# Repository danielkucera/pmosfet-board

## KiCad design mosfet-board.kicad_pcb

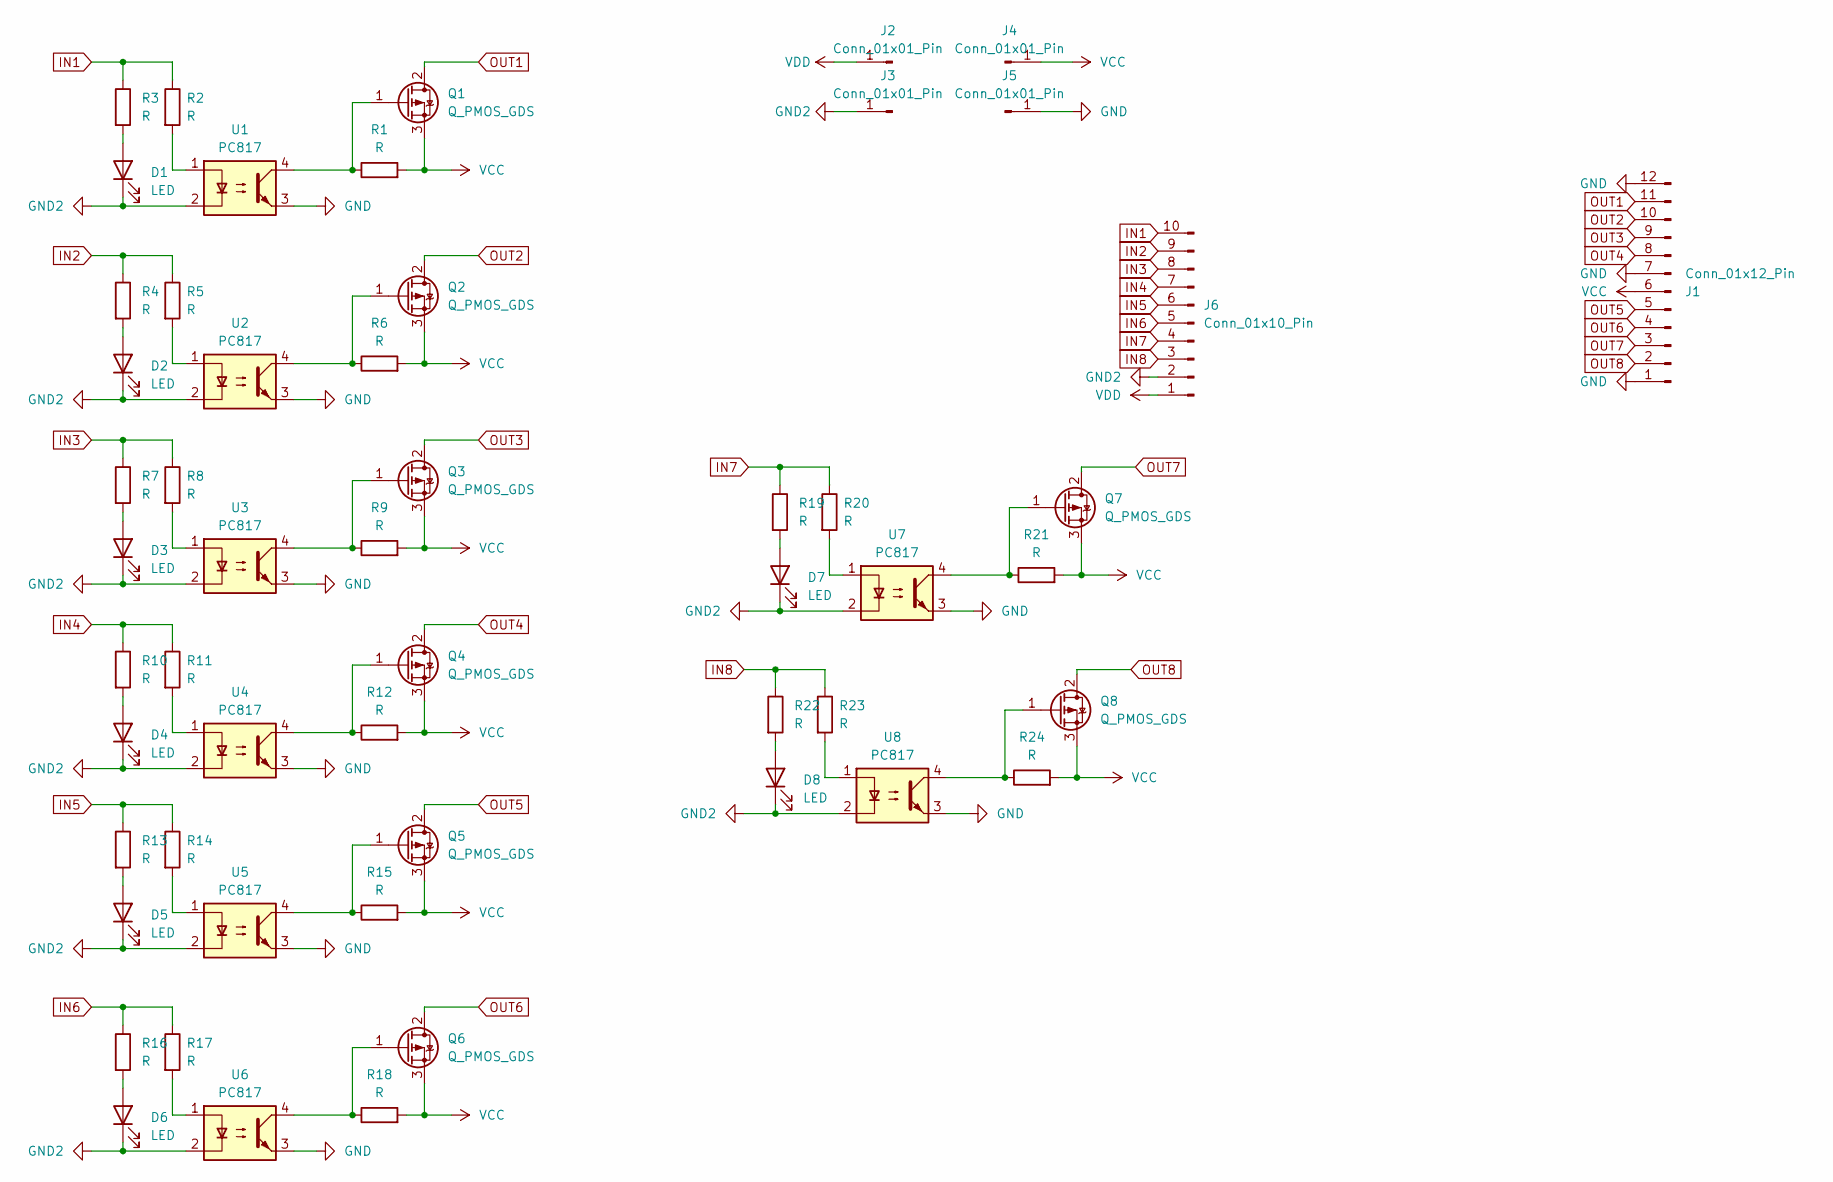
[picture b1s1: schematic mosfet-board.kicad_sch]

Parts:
D1, D2, D3, D4, D5, D6, D7, D8: LED; LED_0603_1608Metric
J1: Conn_01x12_Pin; CONN-TH_12P-P5.08_HT508R-5.08-12P
J2, J3, J4, J5: Conn_01x01_Pin; PinHeader_1x01_P2.54mm_Vertical
J6: Conn_01x10_Pin; PinHeader_1x10_P2.54mm_Vertical
Q1, Q2, Q3, Q4, Q5, Q6, Q7, Q8: Q_PMOS_GDS; TO-252-2
R1, R2, R3, R4, R5, R6, R7, R8, R9, R10, R11, R12, R13, R14, R15, R16, R17, R18, R19, R20, R21, R22, R23, R24: R; R_0603_1608Metric
U1, U2, U3, U4, U5, U6, U7, U8: PC817; DIP-4_W8.89mm_SMDSocket_LongPads

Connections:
GND: J1.1, J1.7, J1.12, J5.1, U1.3, U2.3, U3.3, U4.3, U5.3, U6.3, U7.3, U8.3
GND2: D1.1 (K), D2.1 (K), D3.1 (K), D4.1 (K), D5.1 (K), D6.1 (K), D7.1 (K), D8.1 (K), J3.1, J6.2, U1.2, U2.2, U3.2, U4.2, U5.2, U6.2, U7.2, U8.2
IN1: J6.10, R2.1, R3.1
IN2: J6.9, R4.1, R5.1
IN3: J6.8, R7.1, R8.1
IN4: J6.7, R10.1, R11.1
IN5: J6.6, R13.1, R14.1
IN6: J6.5, R16.1, R17.1
IN7: J6.4, R19.1, R20.1
IN8: J6.3, R22.1, R23.1
unnamed: D1.2 (A), R3.2
unnamed: D2.2 (A), R4.2
unnamed: D3.2 (A), R7.2
unnamed: D4.2 (A), R10.2
unnamed: D5.2 (A), R13.2
unnamed: D6.2 (A), R16.2
unnamed: D7.2 (A), R19.2
unnamed: D8.2 (A), R22.2
unnamed: Q1.1 (G), R1.1, U1.4
unnamed: Q2.1 (G), R6.1, U2.4
unnamed: Q3.1 (G), R9.1, U3.4
unnamed: Q4.1 (G), R12.1, U4.4
unnamed: Q5.1 (G), R15.1, U5.4
unnamed: Q6.1 (G), R18.1, U6.4
unnamed: Q7.1 (G), R21.1, U7.4
unnamed: Q8.1 (G), R24.1, U8.4
unnamed: R2.2, U1.1
unnamed: R5.2, U2.1
unnamed: R8.2, U3.1
unnamed: R11.2, U4.1
unnamed: R14.2, U5.1
unnamed: R17.2, U6.1
unnamed: R20.2, U7.1
unnamed: R23.2, U8.1
OUT1: J1.11, Q1.2 (D)
OUT2: J1.10, Q2.2 (D)
OUT3: J1.9, Q3.2 (D)
OUT4: J1.8, Q4.2 (D)
OUT5: J1.5, Q5.2 (D)
OUT6: J1.4, Q6.2 (D)
OUT7: J1.3, Q7.2 (D)
OUT8: J1.2, Q8.2 (D)
VCC: J1.6, J4.1, Q1.3 (S), Q2.3 (S), Q3.3 (S), Q4.3 (S), Q5.3 (S), Q6.3 (S), Q7.3 (S), Q8.3 (S), R1.2, R6.2, R9.2, R12.2, R15.2, R18.2, R21.2, R24.2
VDD: J2.1, J6.1

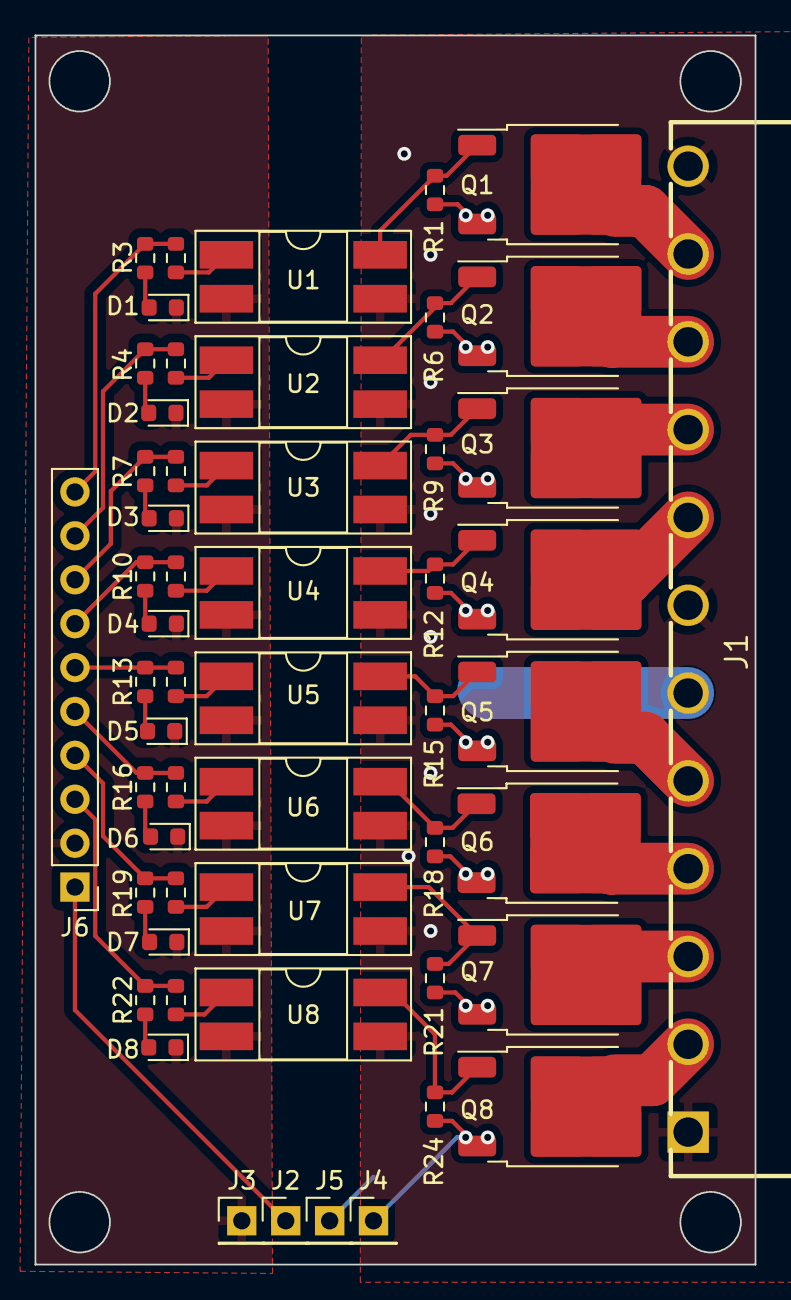
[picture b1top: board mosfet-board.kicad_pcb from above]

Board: 2 copper layers, 41.7 x 71.1 mm, 54 parts (0 on the bottom side), 44 nets.

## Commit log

2024-04-01 v1.1
